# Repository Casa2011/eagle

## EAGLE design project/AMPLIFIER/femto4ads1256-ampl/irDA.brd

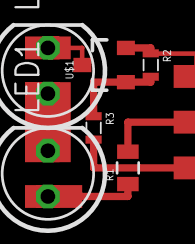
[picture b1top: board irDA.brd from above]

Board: 2 copper layers, 6 parts (0 on the bottom side), 5 nets.

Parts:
LED1, LED2: LED5MM
R1: 50; R0805
R2: 10k; 0603
R3: 100; 0603
U$1: 2N7002; SOT23

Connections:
GND: R2.1, U$1.2
unnamed: LED1.K, LED2.A
unnamed: LED2.K, U$1.3
unnamed: LED1.A, R1.1
unnamed: R2.2, R3.1, U$1.1

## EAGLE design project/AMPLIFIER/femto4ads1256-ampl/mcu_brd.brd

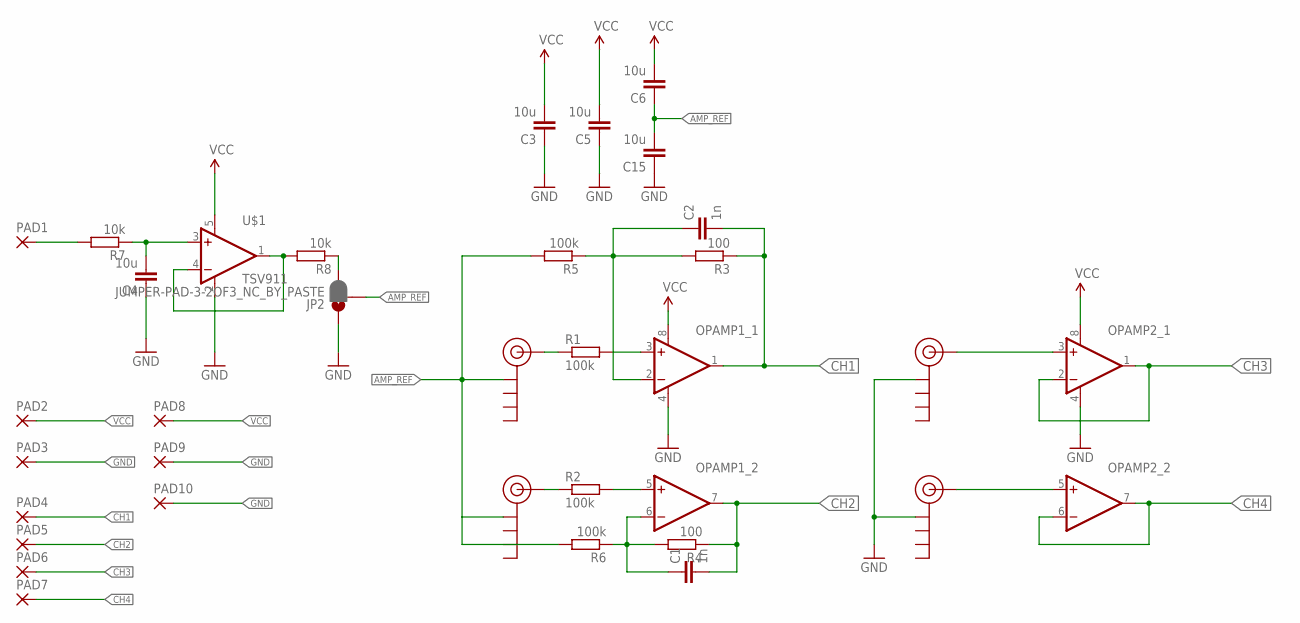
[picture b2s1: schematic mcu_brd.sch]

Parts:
C1, C2: 1n; C0603
C3, C4, C5, C6, C15: 10u; C0805
J$1, J$2, J$3, J$4: SMA_EDGE; SMA-EDGE
JP2: JUMPER-PAD-3-2OF3_NC_BY_PASTE; PAD-JUMPER-3-2OF3_NC_BY_PASTE_YES_SILK_FULL_BOX
OPAMP1, OPAMP2: LMC662; SO08
PAD1, PAD2, PAD3, PAD4, PAD5, PAD6, PAD7, PAD8, PAD9, PAD10: SMD2; SMD1,27-2,54
R1, R2, R5, R6: 100k; 0603
R3, R4: 100; 0603
R7, R8: 10k; 0603
U$1: TSV911; SOT23-5L

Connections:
AMP_REF: C6.1, C15.2, J$1.GND@0 (GND), J$2.GND@0 (GND), JP2.2, R5.2, R6.2
CH1: C2.2, OPAMP1.1 (OUT), PAD4.1, R3.1
CH2: C1.2, OPAMP1.7 (OUT), PAD5.1, R4.1
CH3: OPAMP2.1 (OUT), OPAMP2.2 (-IN), PAD6.1
CH4: OPAMP2.6 (-IN), OPAMP2.7 (OUT), PAD7.1
GND: C3.1, C4.1, C5.1, C15.1, J$3.GND@0 (GND), J$4.GND@0 (GND), JP2.1, OPAMP1.4 (V-), OPAMP2.4 (V-), PAD3.1, PAD9.1, PAD10.1, U$1.2 (V-)
unnamed: J$2.SIG (SIGNAL), R2.1
unnamed: J$1.SIG (SIGNAL), R1.1
unnamed: C2.1, OPAMP1.2 (-IN), R3.2, R5.1
unnamed: C1.1, OPAMP1.6 (-IN), R4.2, R6.1
unnamed: R8.2, U$1.1 (OUT), U$1.4 (-IN)
unnamed: OPAMP1.3 (+IN), R1.2
unnamed: OPAMP1.5 (+IN), R2.2
unnamed: C4.2, R7.1, U$1.3 (+IN)
unnamed: J$3.SIG (SIGNAL), OPAMP2.3 (+IN)
unnamed: J$4.SIG (SIGNAL), OPAMP2.5 (+IN)
unnamed: JP2.3, R8.1
REFIN: PAD1.1, R7.2
VCC: C3.2, C5.2, C6.2, OPAMP1.8 (V+), OPAMP2.8 (V+), PAD2.1, PAD8.1, U$1.5 (V+)

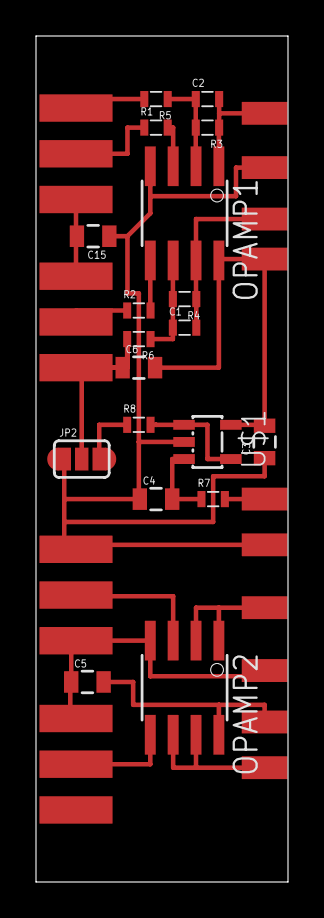
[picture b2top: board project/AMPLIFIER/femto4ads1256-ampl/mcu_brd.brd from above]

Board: 2 copper layers, 14.0 x 47.0 mm, 33 parts (0 on the bottom side), 19 nets.

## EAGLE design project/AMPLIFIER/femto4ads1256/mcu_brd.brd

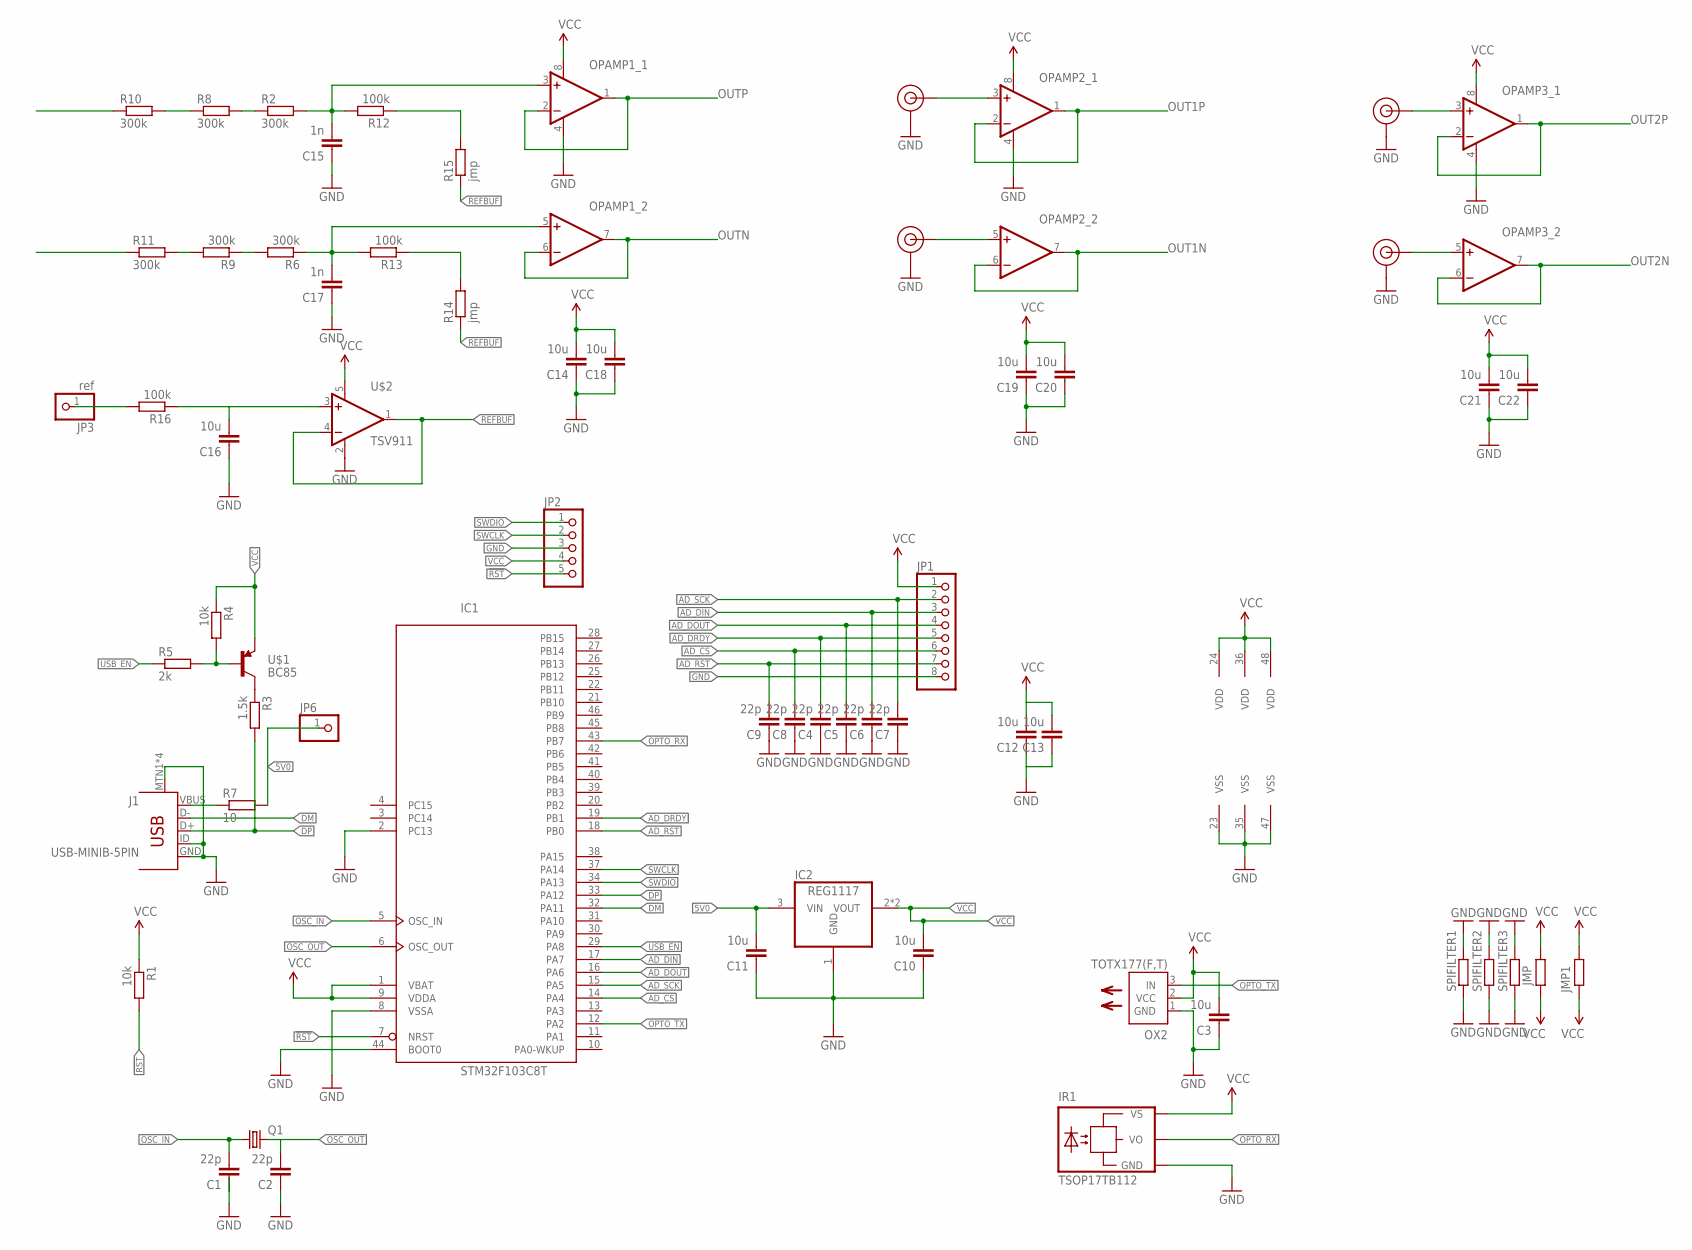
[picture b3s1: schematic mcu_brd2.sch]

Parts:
C1, C2, C4, C5, C6, C7, C8, C9: 22p; C0603
C3: 10u; C0603
C10, C11, C12, C13, C14, C16, C18, C19, C20, C21, C22: 10u; C0805
C15, C17: 1n; C0603
IC1: STM32F103C8T; LQFP48
IC2: REG1117; SOT223
IR1: TSOP17TB112; 1X03
J1: USB-MINIB-5PIN; USB-MINIB
J$1, J$2, J$3, J$4: SMA_EDGE; SMA-EDGE
JMP, JMP1: R0603; 0603
JP1: PINHD-1X8; 1X08
JP2: PINHD-1X5; 1X05
JP3: ref; 1X01M
JP6: PINHD-1X1; 1X01
OPAMP1, OPAMP2, OPAMP3: LMC662; SO08
OX2: TOTX177(F,T); TOTX
Q1: CRYSTALHC49UP; HC49UP
R1, R4: 10k; 0603
R2, R6, R8, R9, R10, R11: 300k; 0603
R3: 1.5k; 0603
R5: 2k; 0603
R7: 10; R0805
R12, R13, R16: 100k; 0603
R14, R15: jmp; 0603
SPIFILTER1, SPIFILTER2, SPIFILTER3: R0603; 0603
U$1: BC85; SOT23
U$2: TSV911; SOT23-5L

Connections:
5V0: C11.2, IC2.3 (VIN), JP6.1, R7.2
!RST: IC1.7 (NRST), JP2.5, R1.2
AD_CS: C8.2, IC1.14 (PA4), JP1.6
AD_DIN: C6.2, IC1.17 (PA7), JP1.3
AD_DOUT: C5.2, IC1.16 (PA6), JP1.4
AD_DRDY: C4.2, IC1.19 (PB1), JP1.5
AD_RST: C9.2, IC1.18 (PB0), JP1.7
AD_SCK: C7.2, IC1.15 (PA5), JP1.2
DM: IC1.32 (PA11), J1.D-
DP: IC1.33 (PA12), J1.D+, R3.2
GND: C1.1, C2.1, C3.1, C4.1, C5.1, C6.1, C7.1, C8.1, C9.1, C10.1, C11.1, C12.1, C13.1, C14.1, C15.1, C16.1, C17.1, C18.1, C19.1, C20.1, C21.1, C22.1, IC1.2 (PC13), IC1.8 (VSSA), IC1.23 (VSS), IC1.35 (VSS), IC1.44 (BOOT0), IC1.47 (VSS), IC2.1 (GND), IR1.3 (GND), J1.GND, J1.ID, J1.MTN1, J1.MTN2 (MTN1), J1.MTN3 (MTN1), J1.MTN4 (MTN1), J$1.GND@0 (GND), J$1.GND@1 (GND), J$1.GND@2 (GND), J$1.GND@3 (GND), J$2.GND@0 (GND), J$2.GND@1 (GND), J$2.GND@2 (GND), J$2.GND@3 (GND), J$3.GND@0 (GND), J$3.GND@1 (GND), J$3.GND@2 (GND), J$3.GND@3 (GND), J$4.GND@0 (GND), J$4.GND@1 (GND), J$4.GND@2 (GND), J$4.GND@3 (GND), JP1.8, JP2.3, OPAMP1.4 (V-), OPAMP2.4 (V-), OPAMP3.4 (V-), OX2.1 (GND), SPIFILTER1.1, SPIFILTER1.2, SPIFILTER2.1, SPIFILTER2.2, SPIFILTER3.1, SPIFILTER3.2, U$2.2 (V-)
unnamed: J$2.SIG (SIGNAL), OPAMP2.5 (+IN)
unnamed: J$1.SIG (SIGNAL), OPAMP2.3 (+IN)
unnamed: R3.1, U$1.3 (C)
unnamed: R4.2, R5.2, U$1.1 (B)
unnamed: J$4.SIG (SIGNAL), OPAMP3.5 (+IN)
unnamed: C17.2, OPAMP1.5 (+IN), R6.1, R13.2
unnamed: J$3.SIG (SIGNAL), OPAMP3.3 (+IN)
unnamed: R12.1, R15.2
unnamed: C15.2, OPAMP1.3 (+IN), R2.2, R12.2
unnamed: R6.2, R9.1
unnamed: R2.1, R8.2
unnamed: R9.2, R11.2
unnamed: R8.1, R10.2
unnamed: JP3.1, R16.2
unnamed: R13.1, R14.2
unnamed: C16.2, R16.1, U$2.3 (+IN)
OPTO_RX: IC1.43 (PB7), IR1.1 (VO)
OPTO_TX: IC1.12 (PA2), OX2.3 (IN)
OSC_IN: C1.2, IC1.5 (OSC_IN), Q1.1
OSC_OUT: C2.2, IC1.6 (OSC_OUT), Q1.2
OUT1N: OPAMP2.6 (-IN), OPAMP2.7 (OUT)
OUT1P: OPAMP2.1 (OUT), OPAMP2.2 (-IN)
OUT2N: OPAMP3.6 (-IN), OPAMP3.7 (OUT)
OUT2P: OPAMP3.1 (OUT), OPAMP3.2 (-IN)
OUTN: OPAMP1.6 (-IN), OPAMP1.7 (OUT)
OUTP: OPAMP1.1 (OUT), OPAMP1.2 (-IN)
REFBUF: R14.1, R15.1, U$2.1 (OUT), U$2.4 (-IN)
SWCLK: IC1.37 (PA14), JP2.2
SWDIO: IC1.34 (PA13), JP2.1
USB_EN: IC1.29 (PA8), R5.1
VBUS: J1.VBUS, R7.1
VCC: C3.2, C10.2, C12.2, C13.2, C14.2, C18.2, C19.2, C20.2, C21.2, C22.2, IC1.1 (VBAT), IC1.9 (VDDA), IC1.24 (VDD), IC1.36 (VDD), IC1.48 (VDD), IC2.2 (VOUT), IC2.4 (VOUT), IR1.2 (VS), JMP.1, JMP.2, JMP1.1, JMP1.2, JP1.1, JP2.4, OPAMP1.8 (V+), OPAMP2.8 (V+), OPAMP3.8 (V+), OX2.2 (VCC), R1.1, R4.1, U$1.2 (E), U$2.5 (V+)

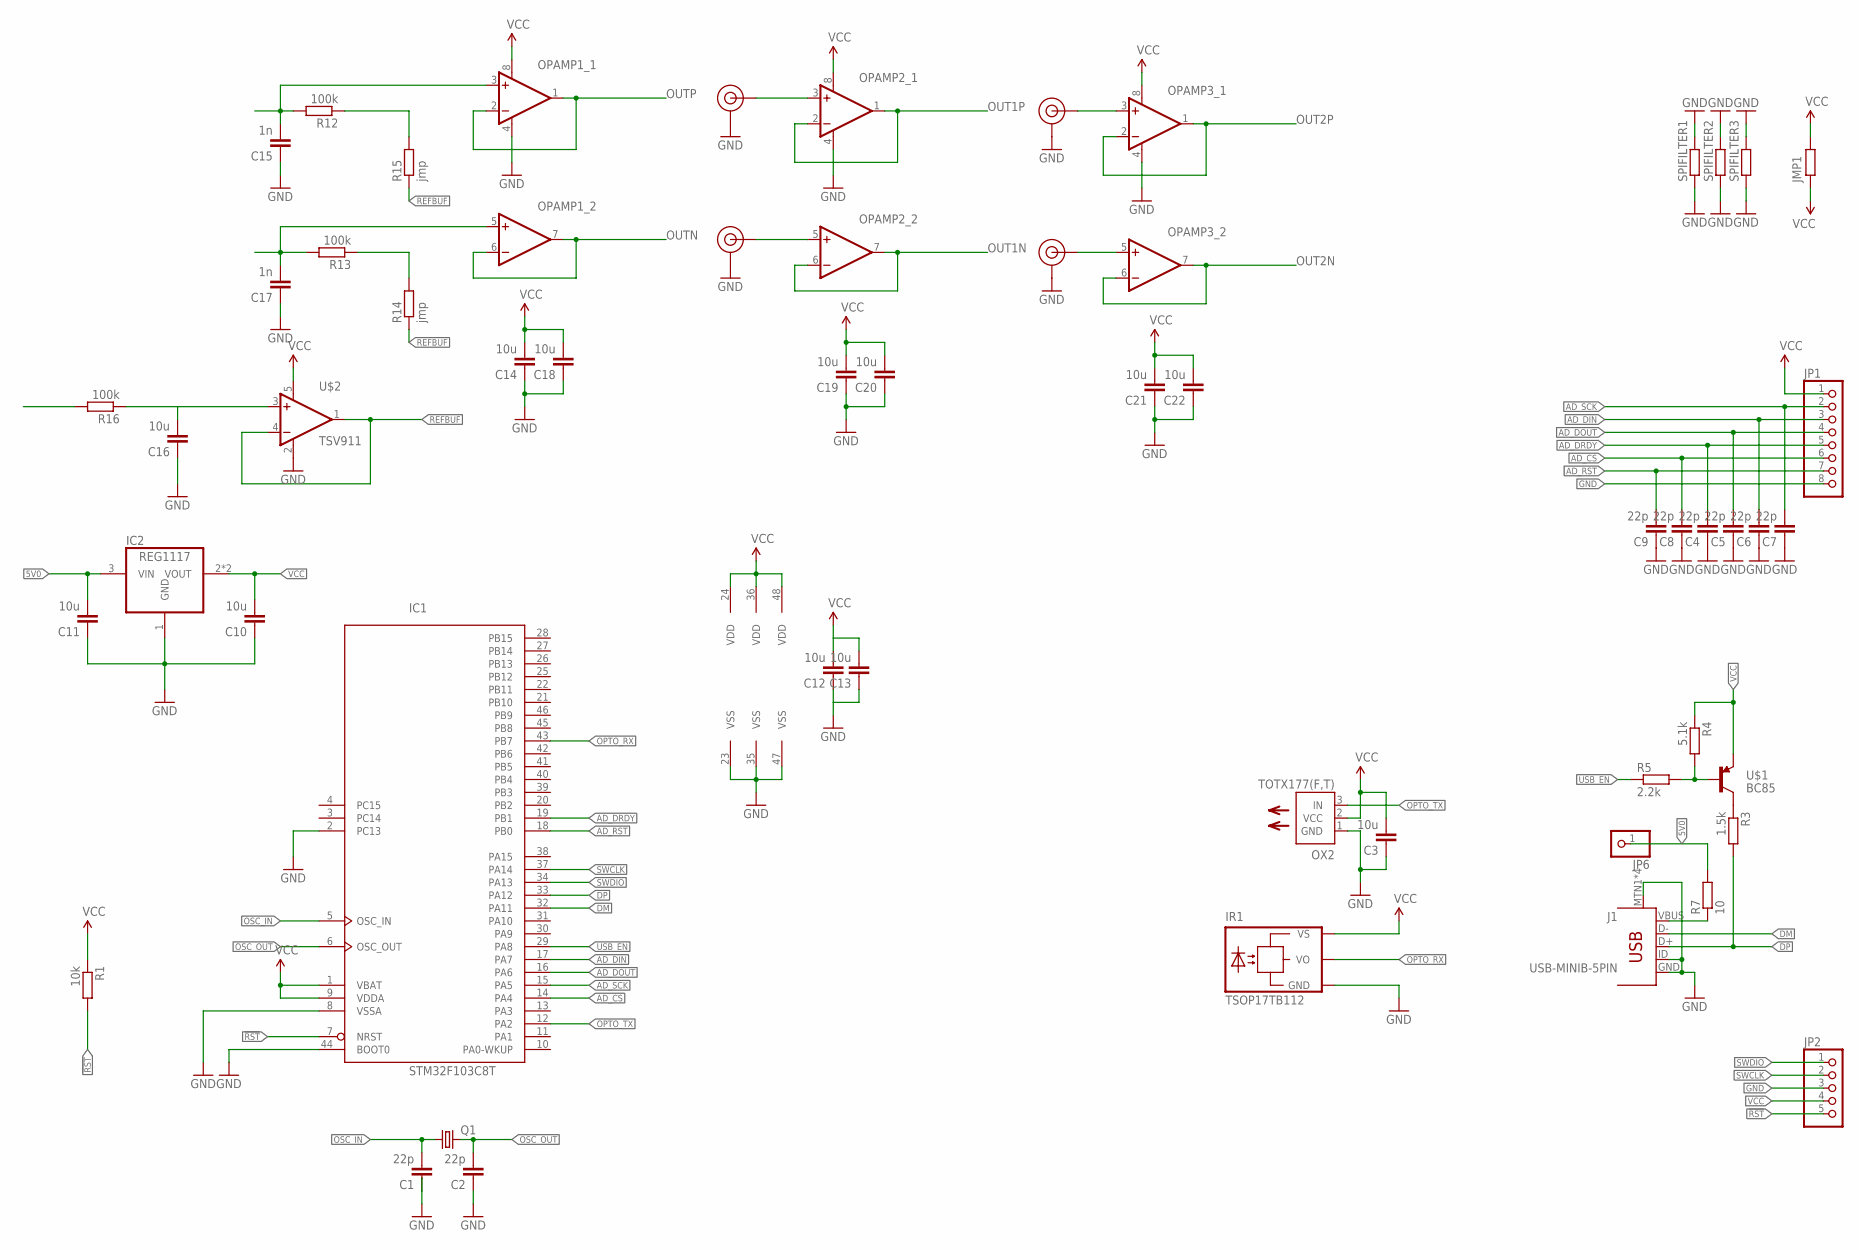
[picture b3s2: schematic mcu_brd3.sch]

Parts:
C1, C2, C4, C5, C6, C7, C8, C9: 22p; C0603
C3: 10u; C0603
C10, C11, C12, C13, C14, C16, C18, C19, C20, C21, C22: 10u; C0805
C15, C17: 1n; C0603
IC1: STM32F103C8T; LQFP48
IC2: REG1117; SOT223
IR1: TSOP17TB112; 1X03
J1: USB-MINIB-5PIN; USB-MINIB
J$1, J$2, J$3, J$4: SMA_EDGE; SMA-EDGE
JMP1: R0603; 0603
JP1: PINHD-1X8; 1X08
JP2: PINHD-1X5; 1X05
JP6: PINHD-1X1; 1X01
OPAMP1, OPAMP2, OPAMP3: LMC662; SO08
OX2: TOTX177(F,T); TOTX
Q1: CRYSTALHC49UP; HC49UP
R1: 10k; 0603
R3: 1.5k; 0603
R4: 5.1k; 0603
R5: 2.2k; 0603
R7: 10; R0805
R12, R13, R16: 100k; 0603
R14, R15: jmp; 0603
SPIFILTER1, SPIFILTER2, SPIFILTER3: R0603; 0603
U$1: BC85; SOT23
U$2: TSV911; SOT23-5L

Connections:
5V0: C11.2, IC2.3 (VIN), JP6.1, R7.2
!RST: IC1.7 (NRST), JP2.5, R1.2
AD_CS: C8.2, IC1.14 (PA4), JP1.6
AD_DIN: C6.2, IC1.17 (PA7), JP1.3
AD_DOUT: C5.2, IC1.16 (PA6), JP1.4
AD_DRDY: C4.2, IC1.19 (PB1), JP1.5
AD_RST: C9.2, IC1.18 (PB0), JP1.7
AD_SCK: C7.2, IC1.15 (PA5), JP1.2
DM: IC1.32 (PA11), J1.D-
DP: IC1.33 (PA12), J1.D+, R3.2
GND: C1.1, C2.1, C3.1, C4.1, C5.1, C6.1, C7.1, C8.1, C9.1, C10.1, C11.1, C12.1, C13.1, C14.1, C15.1, C16.1, C17.1, C18.1, C19.1, C20.1, C21.1, C22.1, IC1.2 (PC13), IC1.8 (VSSA), IC1.23 (VSS), IC1.35 (VSS), IC1.44 (BOOT0), IC1.47 (VSS), IC2.1 (GND), IR1.3 (GND), J1.GND, J1.ID, J1.MTN1, J1.MTN2 (MTN1), J1.MTN3 (MTN1), J1.MTN4 (MTN1), J$1.GND@0 (GND), J$1.GND@1 (GND), J$1.GND@2 (GND), J$1.GND@3 (GND), J$2.GND@0 (GND), J$2.GND@1 (GND), J$2.GND@2 (GND), J$2.GND@3 (GND), J$3.GND@0 (GND), J$3.GND@1 (GND), J$3.GND@2 (GND), J$3.GND@3 (GND), J$4.GND@0 (GND), J$4.GND@1 (GND), J$4.GND@2 (GND), J$4.GND@3 (GND), JP1.8, JP2.3, OPAMP1.4 (V-), OPAMP2.4 (V-), OPAMP3.4 (V-), OX2.1 (GND), SPIFILTER1.1, SPIFILTER1.2, SPIFILTER2.1, SPIFILTER2.2, SPIFILTER3.1, SPIFILTER3.2, U$2.2 (V-)
unnamed: J$2.SIG (SIGNAL), OPAMP2.5 (+IN)
unnamed: J$1.SIG (SIGNAL), OPAMP2.3 (+IN)
unnamed: R3.1, U$1.3 (C)
unnamed: R4.2, R5.2, U$1.1 (B)
unnamed: J$4.SIG (SIGNAL), OPAMP3.5 (+IN)
unnamed 16: C17.2, OPAMP1.5 (+IN), R13.2; also elsewhere on the board
unnamed: J$3.SIG (SIGNAL), OPAMP3.3 (+IN)
unnamed: R12.1, R15.2
unnamed 19: C15.2, OPAMP1.3 (+IN), R12.2; also elsewhere on the board
unnamed 26: R16.2; also elsewhere on the board
unnamed: R13.1, R14.2
unnamed: C16.2, R16.1, U$2.3 (+IN)
OPTO_RX: IC1.43 (PB7), IR1.1 (VO)
OPTO_TX: IC1.12 (PA2), OX2.3 (IN)
OSC_IN: C1.2, IC1.5 (OSC_IN), Q1.1
OSC_OUT: C2.2, IC1.6 (OSC_OUT), Q1.2
OUT1N: OPAMP2.6 (-IN), OPAMP2.7 (OUT)
OUT1P: OPAMP2.1 (OUT), OPAMP2.2 (-IN)
OUT2N: OPAMP3.6 (-IN), OPAMP3.7 (OUT)
OUT2P: OPAMP3.1 (OUT), OPAMP3.2 (-IN)
OUTN: OPAMP1.6 (-IN), OPAMP1.7 (OUT)
OUTP: OPAMP1.1 (OUT), OPAMP1.2 (-IN)
REFBUF: R14.1, R15.1, U$2.1 (OUT), U$2.4 (-IN)
SWCLK: IC1.37 (PA14), JP2.2
SWDIO: IC1.34 (PA13), JP2.1
USB_EN: IC1.29 (PA8), R5.1
VBUS: J1.VBUS, R7.1
VCC: C3.2, C10.2, C12.2, C13.2, C14.2, C18.2, C19.2, C20.2, C21.2, C22.2, IC1.1 (VBAT), IC1.9 (VDDA), IC1.24 (VDD), IC1.36 (VDD), IC1.48 (VDD), IC2.2 (VOUT), IC2.4 (VOUT), IR1.2 (VS), JMP1.1, JMP1.2, JP1.1, JP2.4, OPAMP1.8 (V+), OPAMP2.8 (V+), OPAMP3.8 (V+), OX2.2 (VCC), R1.1, R4.1, U$1.2 (E), U$2.5 (V+); also elsewhere on the board

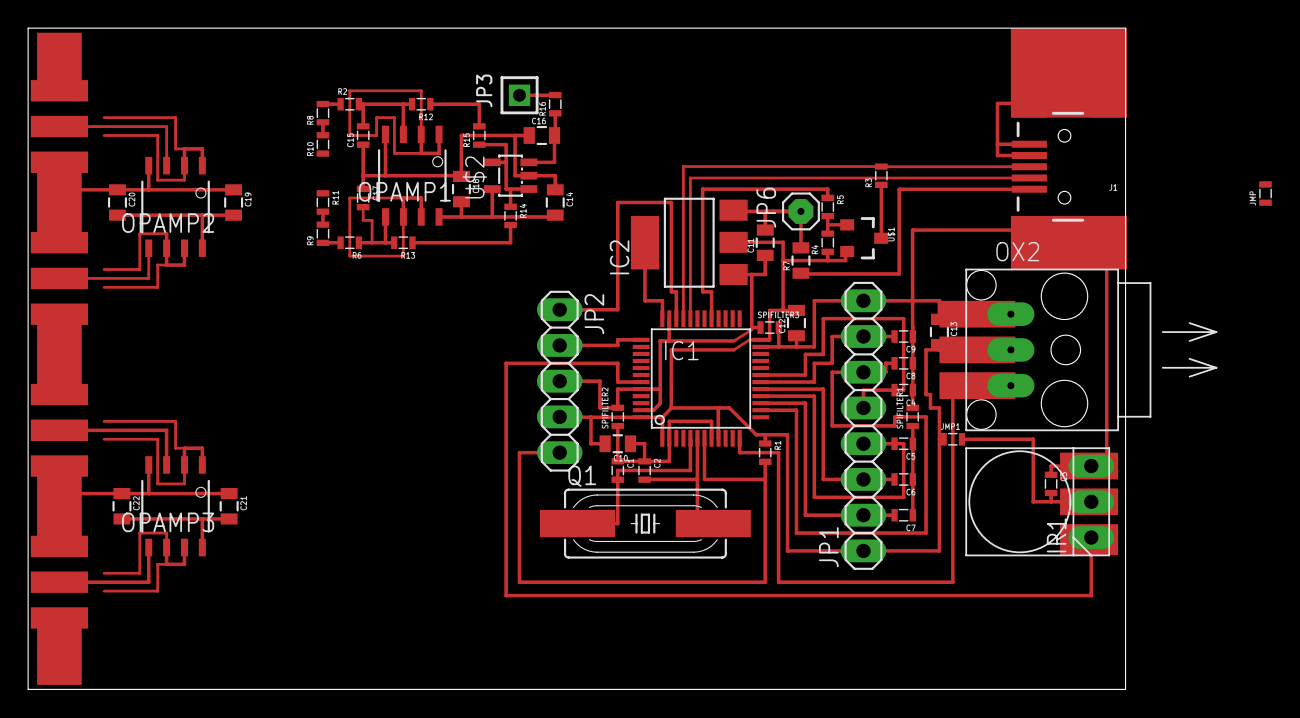
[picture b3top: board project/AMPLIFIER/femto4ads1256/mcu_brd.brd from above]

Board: 2 copper layers, 78.0 x 47.0 mm, 62 parts (0 on the bottom side), 43 nets.

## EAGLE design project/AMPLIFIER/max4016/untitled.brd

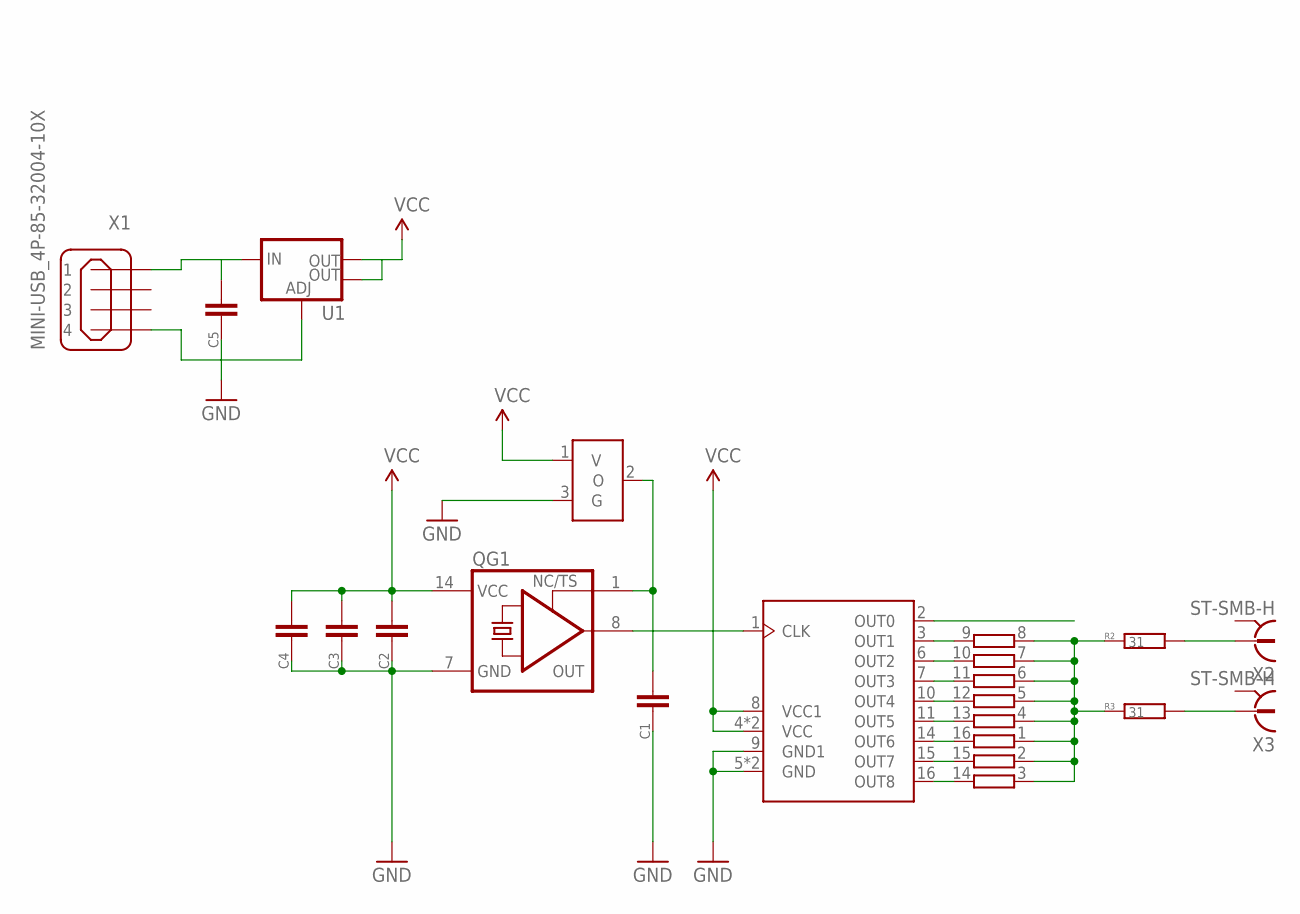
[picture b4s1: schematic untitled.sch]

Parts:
C1, C2, C3, C4, C5: CC0805; C0805
QG1: XO-14; DIL14S
R1: 4816P-T01; 4816P
R2, R3: 31; R0805
U1: V_REG_LM1117SOT223; SOT223
U$2: CY2309NZ; SOIC127P600X175-16N
U$3: REF3025; SOT23
X1: MINI-USB_4P-85-32004-10X; 85-32004-10X
X2, X3: ST-SMB-H

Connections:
GND: C1.2, C2.2, C3.2, C4.2, C5.2, QG1.7 (GND), U1.1 (ADJ), U$2.5 (GND), U$2.9 (GND1), U$2.12 (GND), U$3.3 (G), X1.4
unnamed: QG1.8 (OUT), U$2.1 (CLK)
unnamed: R1.9 (1), U$2.3 (OUT1)
unnamed: R1.10 (2), U$2.6 (OUT2)
unnamed: R1.11 (2), U$2.7 (OUT3)
unnamed: R1.12 (2), U$2.10 (OUT4)
unnamed: R1.1, R1.2 (1), R1.3 (1), R1.4 (1), R1.5 (1), R1.6 (1), R1.7 (1), R1.8 (2), R2.1, R3.1
unnamed: R1.13 (2), U$2.11 (OUT5)
unnamed: R1.16 (2), U$2.14 (OUT6)
unnamed: R1.15 (2), U$2.15 (OUT7)
unnamed: R1.14 (2), U$2.16 (OUT8)
unnamed: R2.2, X2.1
unnamed: R3.2, X3.1
unnamed: C1.1, QG1.1 (TS), U$3.2 (O)
unnamed: C5.1, U1.3 (IN), X1.1
VCC: C2.1, C3.1, C4.1, QG1.14 (VCC), U1.2 (OUT), U1.4 (OUT), U$2.4 (VCC), U$2.8 (VCC1), U$2.13 (VCC), U$3.1 (V)

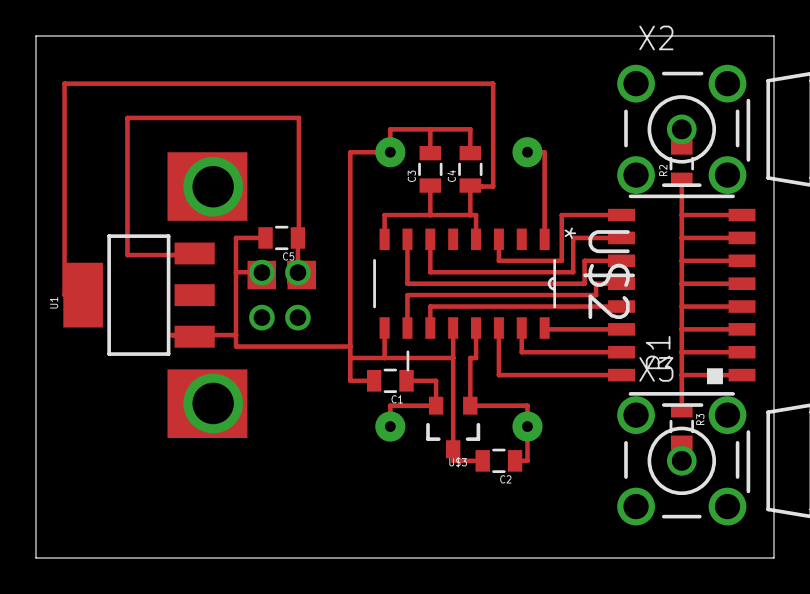
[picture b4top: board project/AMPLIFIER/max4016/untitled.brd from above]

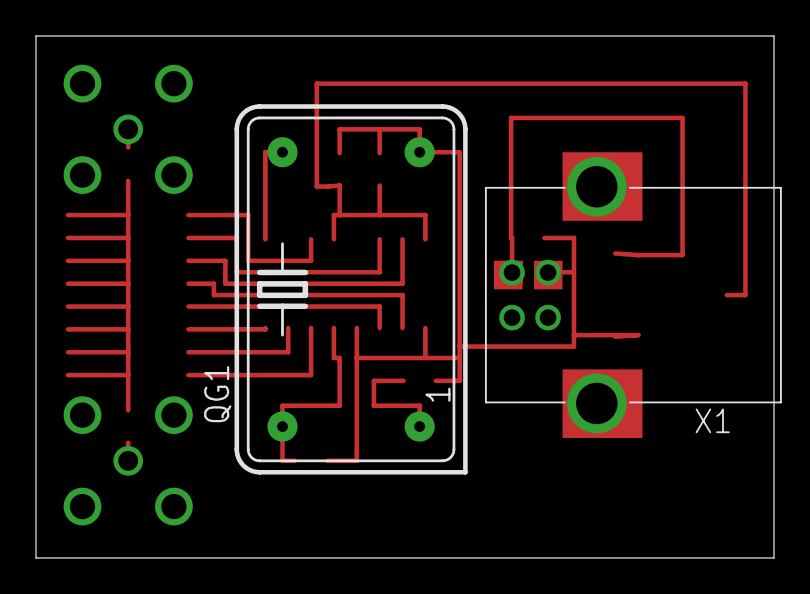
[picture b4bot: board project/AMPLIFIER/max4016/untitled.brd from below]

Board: 2 copper layers, 41.0 x 29.0 mm, 15 parts (2 on the bottom side), 16 nets.

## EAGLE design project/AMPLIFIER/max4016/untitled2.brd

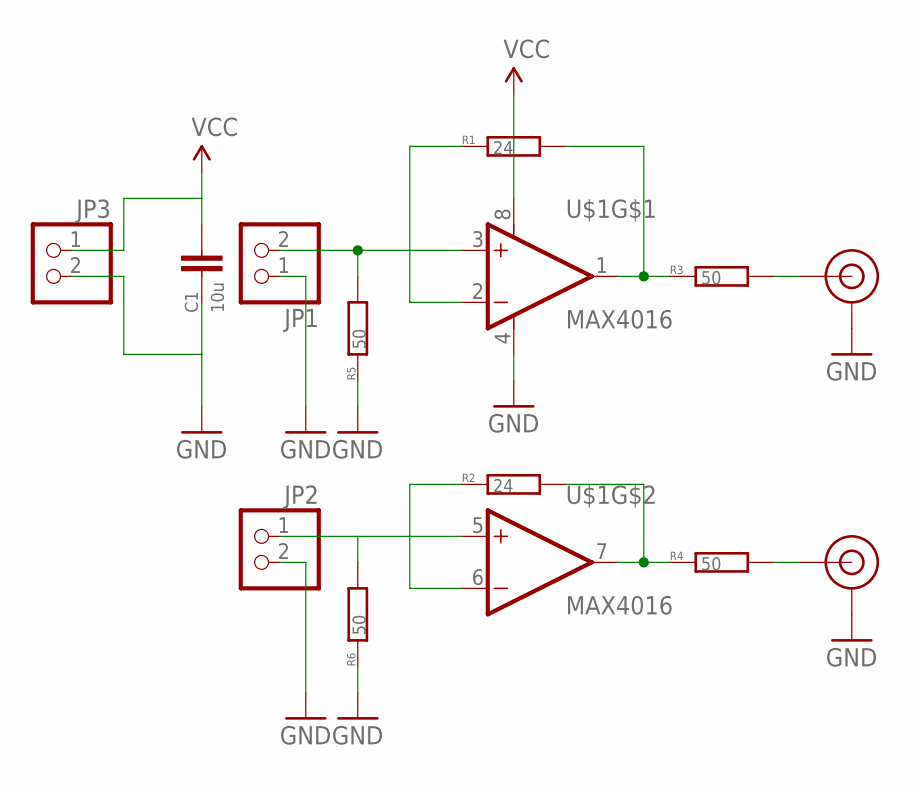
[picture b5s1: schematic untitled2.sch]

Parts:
C1: 10u; C0805
J$1, J$2: SMA_EDGE; SMA-EDGE
JP1, JP2, JP3: PINHD-1X02_2.54; 1X02
R1, R2: 24; 0603
R3, R4, R5, R6: 50; 0603
U$1: MAX4016; SO08

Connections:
GND: C1.2, J$1.GND@0 (GND), J$1.GND@1 (GND), J$1.GND@2 (GND), J$1.GND@3 (GND), J$2.GND@0 (GND), J$2.GND@1 (GND), J$2.GND@2 (GND), J$2.GND@3 (GND), JP1.1, JP2.2, JP3.2, R5.1, R6.1, U$1.4 (V-)
unnamed: R1.2, R3.1, U$1.1 (OUT)
unnamed: R2.2, R4.1, U$1.7 (OUT)
unnamed: J$2.SIG (SIGNAL), R4.2
unnamed: J$1.SIG (SIGNAL), R3.2
unnamed: R1.1, U$1.2 (-IN)
unnamed: R2.1, U$1.6 (-IN)
unnamed: JP2.1, R6.2, U$1.5 (+IN)
unnamed: JP1.2, R5.2, U$1.3 (+IN)
VCC: C1.1, JP3.1, U$1.8 (V+)

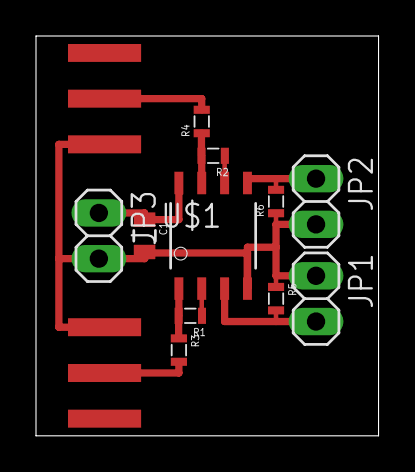
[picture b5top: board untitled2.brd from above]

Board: 2 copper layers, 19.0 x 22.2 mm, 13 parts (0 on the bottom side), 10 nets.

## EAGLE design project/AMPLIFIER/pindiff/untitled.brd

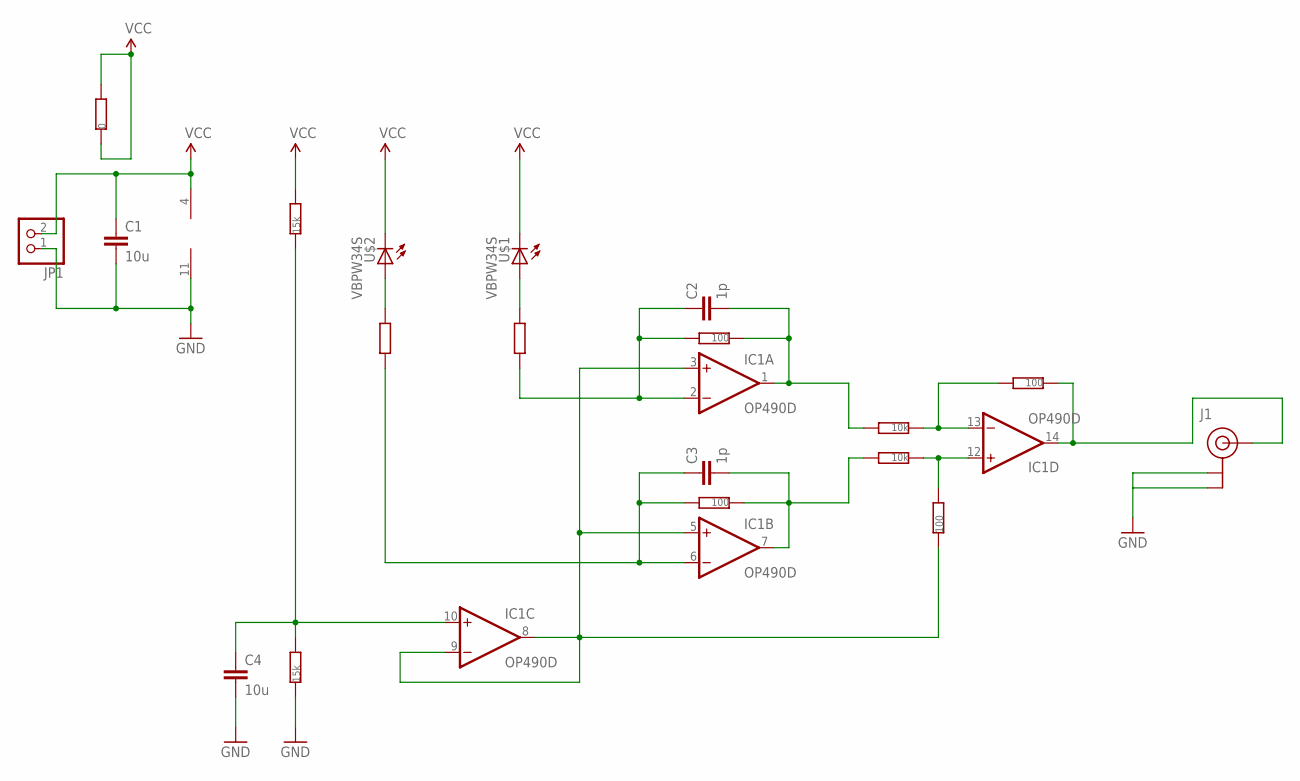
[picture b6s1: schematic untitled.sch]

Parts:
C1, C4: 10u; C0805
C2, C3: 1p; C0603
IC1: OP490D; SO14
J1: U.FL
JP1: PINHD-1X2; 1X02
R1, R2: R0603; 0603
R3, R4, R9, R10: 100; 0603
R5, R6: 15k; 0603
R7, R8: 10k; 0603
R11: 0; 0603
U$1, U$2: VBPW34S; SMD_PIN

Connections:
GND: C1.2, C4.2, IC1.11 (V-), J1.P$1 (GND), J1.P$2 (GND), JP1.1, R6.1
unnamed: R1.2, U$1.A
unnamed: R2.2, U$2.A
unnamed: C2.1, IC1.2 (-IN), R1.1, R3.2
unnamed: C3.1, IC1.6 (-IN), R2.1, R4.2
unnamed: C2.2, IC1.1 (OUT), R3.1, R8.2
unnamed: C3.2, IC1.7 (OUT), R4.1, R7.2
unnamed: C4.1, IC1.10 (+IN), R5.1, R6.2
unnamed: IC1.12 (+IN), R7.1, R10.2
unnamed: IC1.13 (-IN), R8.1, R9.2
unnamed: IC1.14 (OUT), J1.P$3 (SIGNAL), R9.1
unnamed: IC1.3 (+IN), IC1.5 (+IN), IC1.8 (OUT), IC1.9 (-IN), R10.1
VCC: C1.1, IC1.4 (V+), JP1.2, R5.2, R11.1, R11.2, U$1.K (C), U$2.K (C)

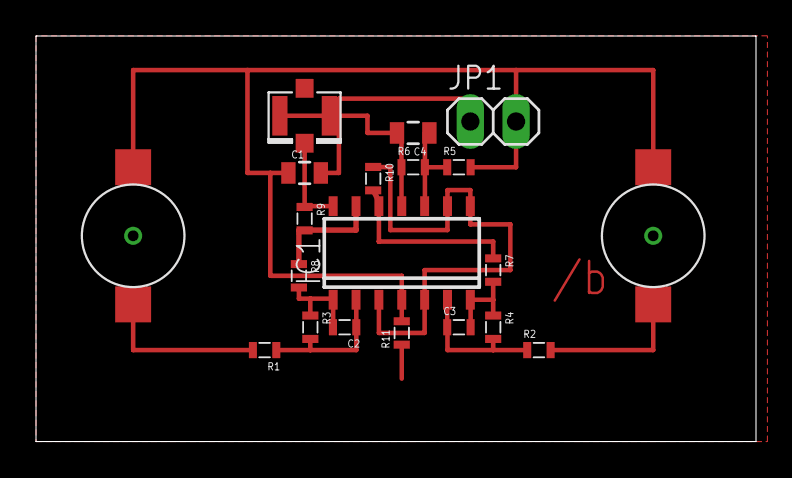
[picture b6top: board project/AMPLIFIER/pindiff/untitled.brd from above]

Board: 2 copper layers, 40.0 x 22.5 mm, 20 parts (0 on the bottom side), 13 nets.

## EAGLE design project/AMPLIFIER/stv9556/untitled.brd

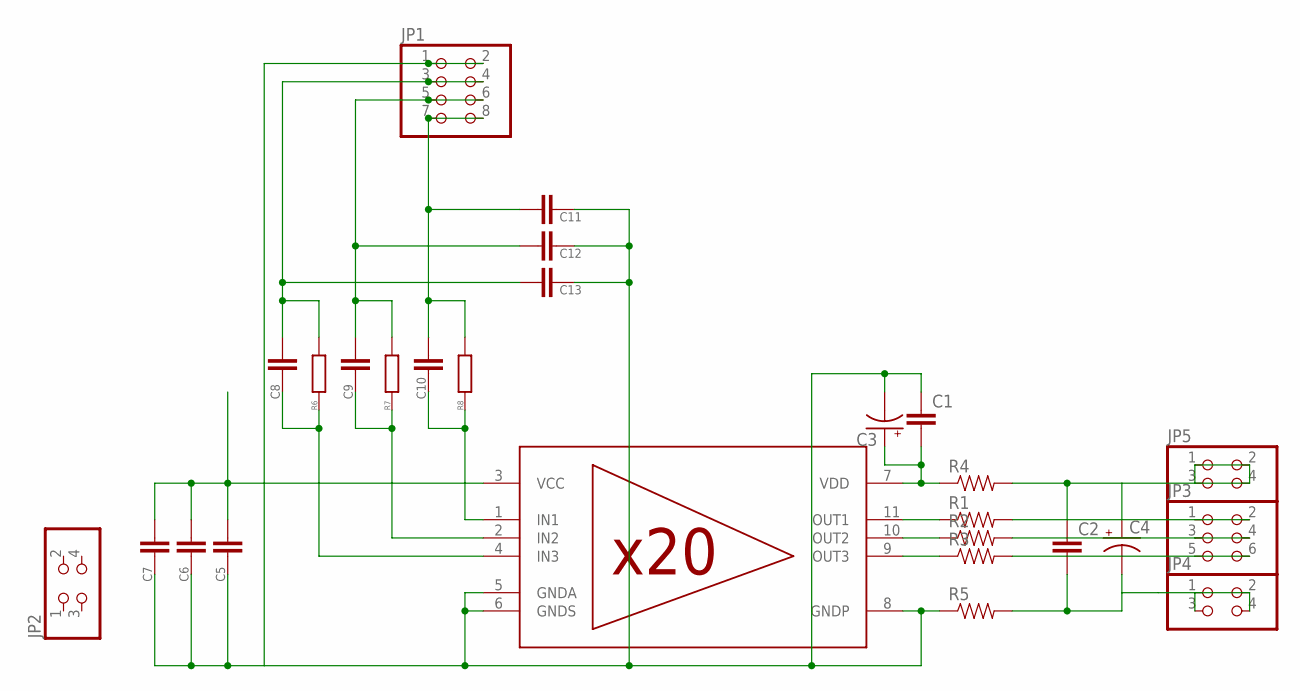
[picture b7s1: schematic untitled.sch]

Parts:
C1, C2: CAPPTH1; CAP-PTH-5MM
C3, C4: CPOL-USE5-8.5; E5-8,5
C5, C6, C7, C8, C9, C10, C11, C12, C13: CC0805; C0805
JP1: PINHD-2X04_2.54-SMD; 2X04SMD
JP2, JP4, JP5: PINHD-2X02_2.54-SMD; 2X02SMD
JP3: PINHD-2X03_2.54-SMD; 2X03SMD
R1, R2, R3, R4, R5: RESISTORPTH-1/2W; AXIAL-0.5
R6, R7, R8: R0805
U$1: STV9556; TA11B

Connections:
unnamed: R1.P$1 (1), U$1.11 (OUT1)
unnamed: R2.P$1 (1), U$1.10 (OUT2)
unnamed: R3.P$1 (1), U$1.9 (OUT3)
unnamed: C1.1, C3.-, C5.2, C6.2, C7.2, C11.2, C12.2, C13.2, JP1.1, JP1.2, R5.P$1 (1), U$1.5 (GNDA), U$1.6 (GNDS), U$1.8 (GNDP)
unnamed: C1.2, C3.+, R4.P$1 (1), U$1.7 (VDD)
unnamed: C5.1, C6.1, C7.1, U$1.3 (VCC)
unnamed: JP3.1, JP3.2, R1.P$2 (2)
unnamed: JP3.3, JP3.4, R2.P$2 (2)
unnamed: C10.2, R8.1, U$1.1 (IN1)
unnamed: C9.2, R7.1, U$1.2 (IN2)
unnamed: C8.2, R6.1, U$1.4 (IN3)
unnamed: JP3.5, JP3.6, R3.P$2 (2)
unnamed: C2.2, C4.-, JP4.1, JP4.2, JP4.3, JP4.4, R5.P$2 (2)
unnamed: C8.1, C13.1, JP1.3, JP1.4, R6.2
unnamed: C9.1, C12.1, JP1.5, JP1.6, R7.2
unnamed: C10.1, C11.1, JP1.7, JP1.8, R8.2
unnamed: C2.1, C4.+, JP5.1, JP5.2, JP5.3, JP5.4, R4.P$2 (2)

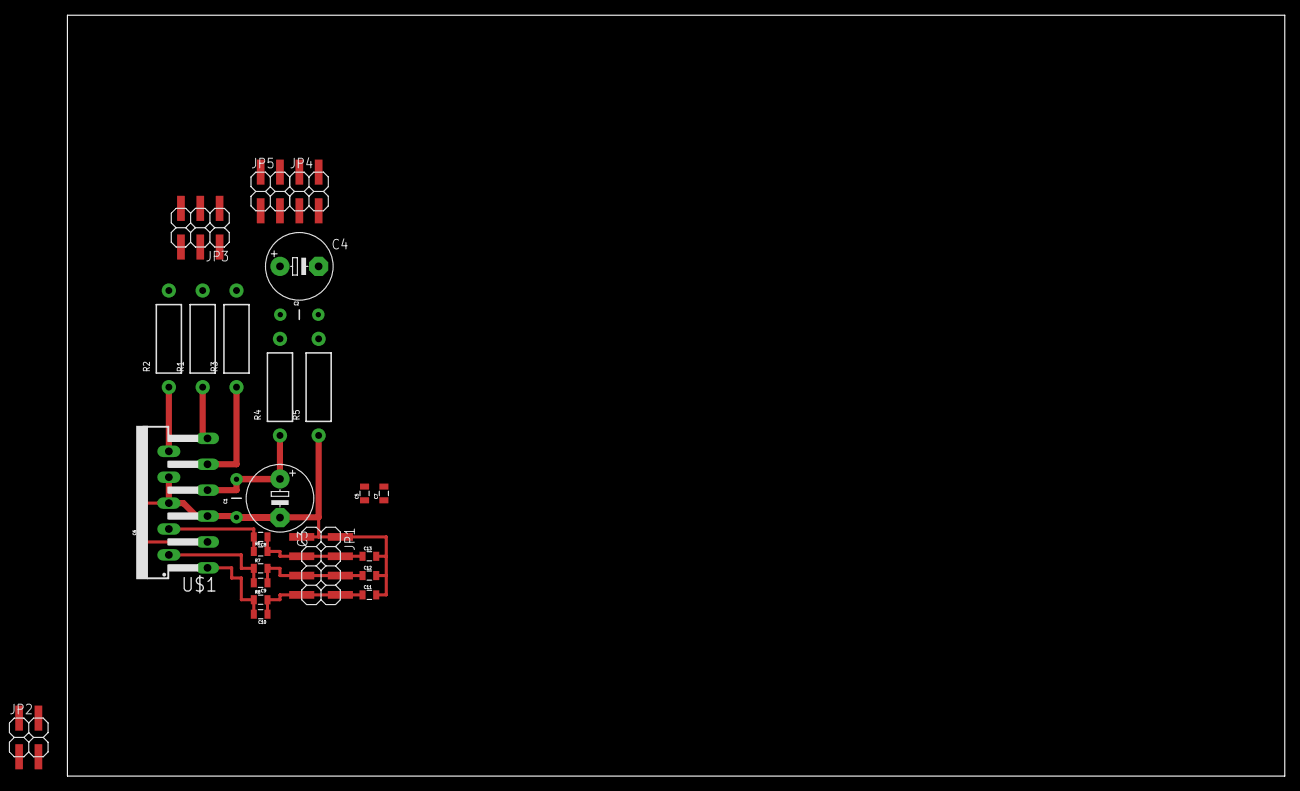
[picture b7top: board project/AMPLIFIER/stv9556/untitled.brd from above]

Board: 2 copper layers, 160.0 x 100.0 mm, 27 parts (0 on the bottom side), 17 nets.

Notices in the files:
parts and their libraries:
SparkFun-Connectors: Licensing: Creative Commons ShareAlike 4.0 International - https://creativecommons.org/licenses/by-sa/4.0
